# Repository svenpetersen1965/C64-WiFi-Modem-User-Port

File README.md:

# C64-WiFi-Modem-User-Port
A NodeMCU (ESP8266) based WiFi modem for the C64's user port
This is a Wifi-Modem for the Commodore C64 Uperport, which is based on the ESP8266 (NodeMCU v3). It contains level shifters to 
translate between the NodeMCU 3.3V level and the User Port 5V level. This prevents stressing the User Port due to a level mismatch.

Further on, status LEDs and (in Rev. 1) a Reset switch is contained.

About the NodeMCU v3: There is a version, which is wider. The version that work is WeMOS NodeMCU v3, which is about 25.4mm wide. You can compare it to this picture, please. The right one has the labeling of the pins parallel to the edge of the PCB. 

The wiring follows the instruction on https://1200baud.wordpress.com/2017/03/04/build-your-own-9600-baud-c64-wifi-modem-for-20/ 

The firmware, required for the NodeMCU, can be obtained from the same website. Please follow the setup procedure described there.

Now, the STL files for a 3D printed case are available for this project.

There are three types of reset switch plungers for some common tact switch heights (4.3mm, 5mm and 7mm).

Rev. 1 works well, but only accepts the (smaller) WeMos NodeMCU v3 (approximately 48mx25mm). There is a bigger version available from the common sales platforms, which are bigger: 31mm x 57mm and don't fit the footprint of Rev. 1. This led to Rev. 2, which is now tested and working completely. 

Both sizes of the NodeMCU

WiFi Modem Rev. 2 in case

A nice blog about this project can be found here: <a href="https://medium.com/@gozdnijezek/c64-wifi-modem-user-port-by-sven-petersen-commodore-wifi-modem-21ab0eed411d">GozdniJezek: C64-WiFi-Modem-User-Port by Sven Petersen (Commodore WiFi modem)</a>

# Recommended Screws
For the case, I have used 2.9mm x 9.5mm (self taping) screws for sheet metal (C 2,9x9,5H, DIN 7981). 

# Calculation of the Component prices
The prices of the components was summed up. The total costs without the 3D printed case and any shipping fees is 16.19€ (May 2020). This might differ, depending on the source of the parts the Node MCU v3 can be obtained from non-domestic sources for less.

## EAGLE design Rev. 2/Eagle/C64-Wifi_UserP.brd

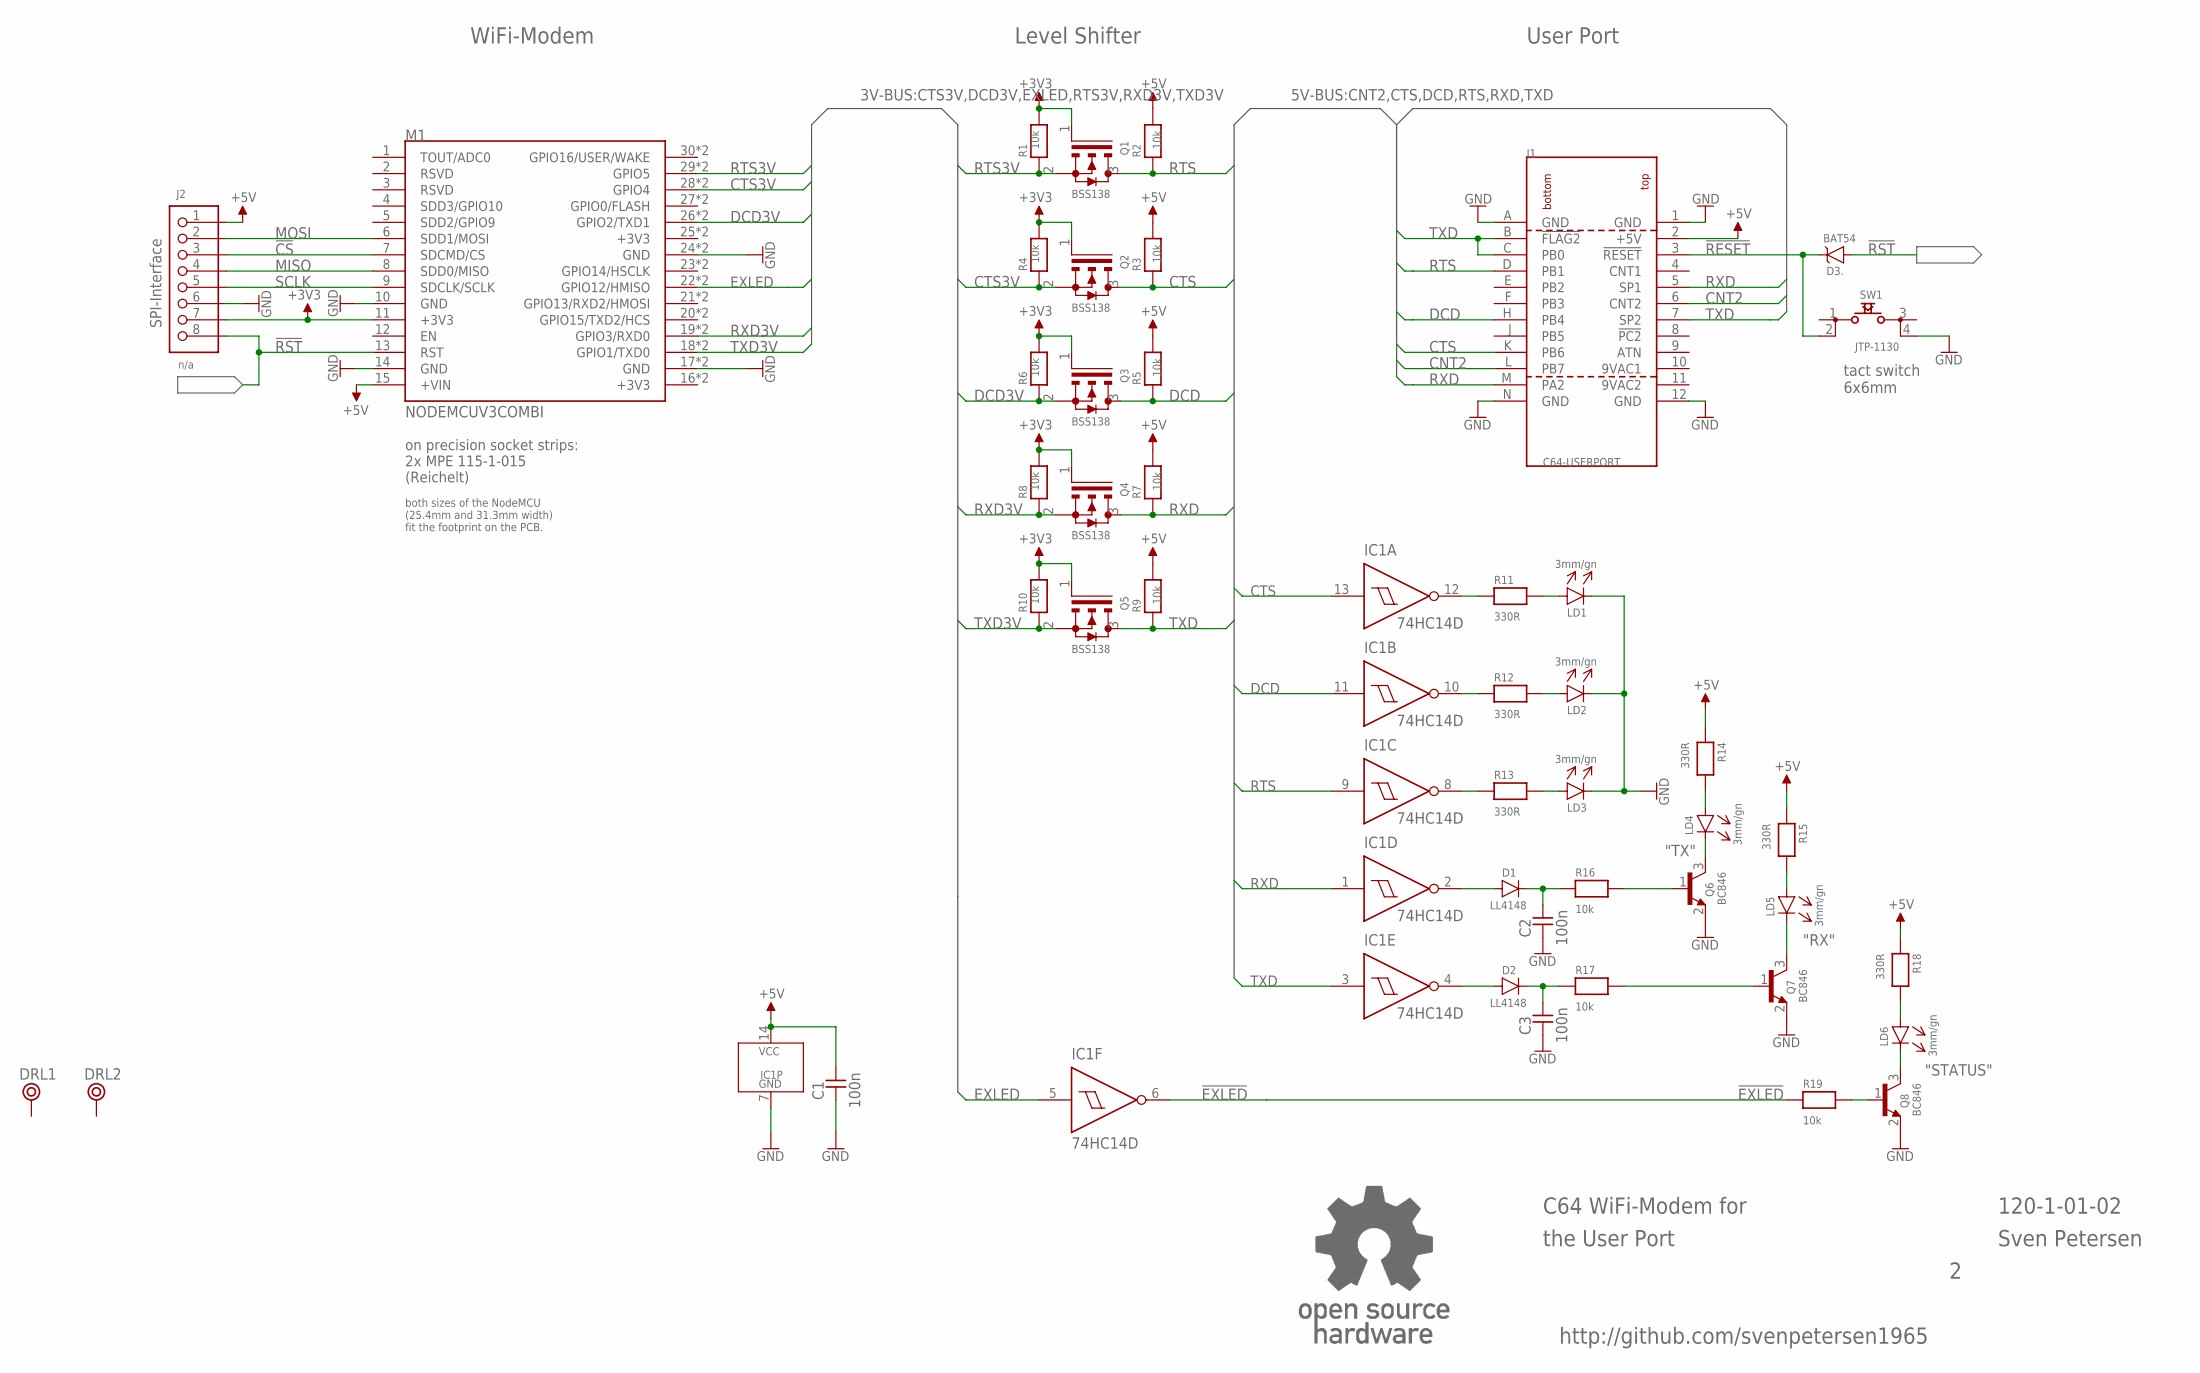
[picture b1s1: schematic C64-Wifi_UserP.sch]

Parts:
C1, C2, C3: 100n; 0805
D1, D2: LL4148; SOD80C
D3: BAT54; SOT23
DRL1, DRL2: BOHR3,3
IC1: 74HC14D; SO-14
J1: C64-USERPORT; USERPORT
J2: n/a; 1X08
LD1, LD2, LD3, LD4, LD5, LD6: 3mm/gn; 3MM
M1: NODEMCUV3COMBI; NODEMCUV3_X
Q1, Q2, Q3, Q4, Q5: BSS138; SOT23
Q6, Q7, Q8: BC846; SOT23
R1, R2, R3, R4, R5, R6, R7, R8, R9, R10, R16, R17, R19: 10k; 0805
R11, R12, R13, R14, R15, R18: 330R; 0805
SW1: JTP-1130
U$45: OPEN_SOURCE_HW; OPENHW

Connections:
9VAC1: J1.10 (9VAC1)
9VAC2: J1.11 (9VAC2)
!CS: J2.3, M1.7 (SDCMD/CS)
!EXLED: IC1.6 (O), R19.1
!RESET: D3.3 (K), J1.3 (!RESET), SW1.2
!RST: D3.1 (A), J2.8, M1.13 (RST)
+3V3: J2.7, M1.11 (+3V3), Q1.1 (G), Q2.1 (G), Q3.1 (G), Q4.1 (G), Q5.1 (G), R1.2, R4.2, R6.2, R8.2, R10.2
+5V: C1.2, IC1.14 (VCC), J1.2 (+5V), J2.1, M1.15 (+VIN), R2.2, R3.2, R5.2, R7.2, R9.2, R14.1, R15.1, R18.1
CNT2: J1.6 (CNT2), J1.L (PB7)
CTS: IC1.13 (I), J1.K (PB6), Q2.3 (D), R3.1
CTS3V: M1.28 (GPIO4), M1.28W (GPIO4), Q2.2 (S), R4.1
DCD: IC1.11 (I), J1.H (PB4), Q3.3 (D), R5.1
DCD3V: M1.26 (GPIO2/TXD1), M1.26W (GPIO2/TXD1), Q3.2 (S), R6.1
EXLED: IC1.5 (I), M1.22 (GPIO12/HMISO), M1.22W (GPIO12/HMISO)
GND: C1.1, C2.1, C3.1, IC1.7 (GND), J1.1 (GND), J1.12 (GND), J1.A (GND), J1.N (GND), J2.6, LD1.C (K), LD2.C (K), LD3.C (K), M1.10 (GND), M1.14 (GND), M1.17 (GND), M1.17W (GND), M1.24 (GND), M1.24W (GND), Q6.2 (E), Q7.2 (E), Q8.2 (E), SW1.4
MISO: J2.4, M1.8 (SDD0/MISO)
MOSI: J2.2, M1.6 (SDD1/MOSI)
unnamed: IC1.12 (O), R11.1
unnamed: IC1.10 (O), R12.1
unnamed: IC1.8 (O), R13.1
unnamed: D1.A, IC1.2 (O)
unnamed: D2.A, IC1.4 (O)
unnamed: LD5.A, R15.2
unnamed: LD4.A, R14.2
unnamed: LD3.A, R13.2
unnamed: LD2.A, R12.2
unnamed: LD1.A, R11.2
unnamed: C2.2, D1.K, R16.1
unnamed: C3.2, D2.K, R17.1
unnamed: Q6.1 (B), R16.2
unnamed: Q7.1 (B), R17.2
unnamed: LD4.C (K), Q6.3 (C)
unnamed: LD5.C (K), Q7.3 (C)
unnamed: LD6.A, R18.2
unnamed: LD6.C (K), Q8.3 (C)
unnamed: Q8.1 (B), R19.2
RTS: IC1.9 (I), J1.D (PB1), Q1.3 (D), R2.1
RTS3V: M1.29 (GPIO5), M1.29W (GPIO5), Q1.2 (S), R1.1
RXD: IC1.1 (I), J1.5 (SP1), J1.M (PA2), Q4.3 (D), R7.1
RXD3V: M1.19 (GPIO3/RXD0), M1.19W (GPIO3/RXD0), Q4.2 (S), R8.1
SCLK: J2.5, M1.9 (SDCLK/SCLK)
TXD: IC1.3 (I), J1.7 (SP2), J1.B (!FLAG2), J1.C (PB0), Q5.3 (D), R9.1
TXD3V: M1.18 (GPIO1/TXD0), M1.18W (GPIO1/TXD0), Q5.2 (S), R10.1

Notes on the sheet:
WiFi-Modem
Level Shifter
User Port
C64 WiFi-Modem for
the User Port
120-1-01-02
Sven Petersen
on precision socket strips: 2x MPE 115-1-015 (Reichelt)
"TX"
"RX"
"STATUS"
SPI-Interface
both sizes of the NodeMCU (25.4mm and 31.3mm width) fit the footprint on the PCB.
http://github.com/svenpetersen1965
tact switch 6x6mm

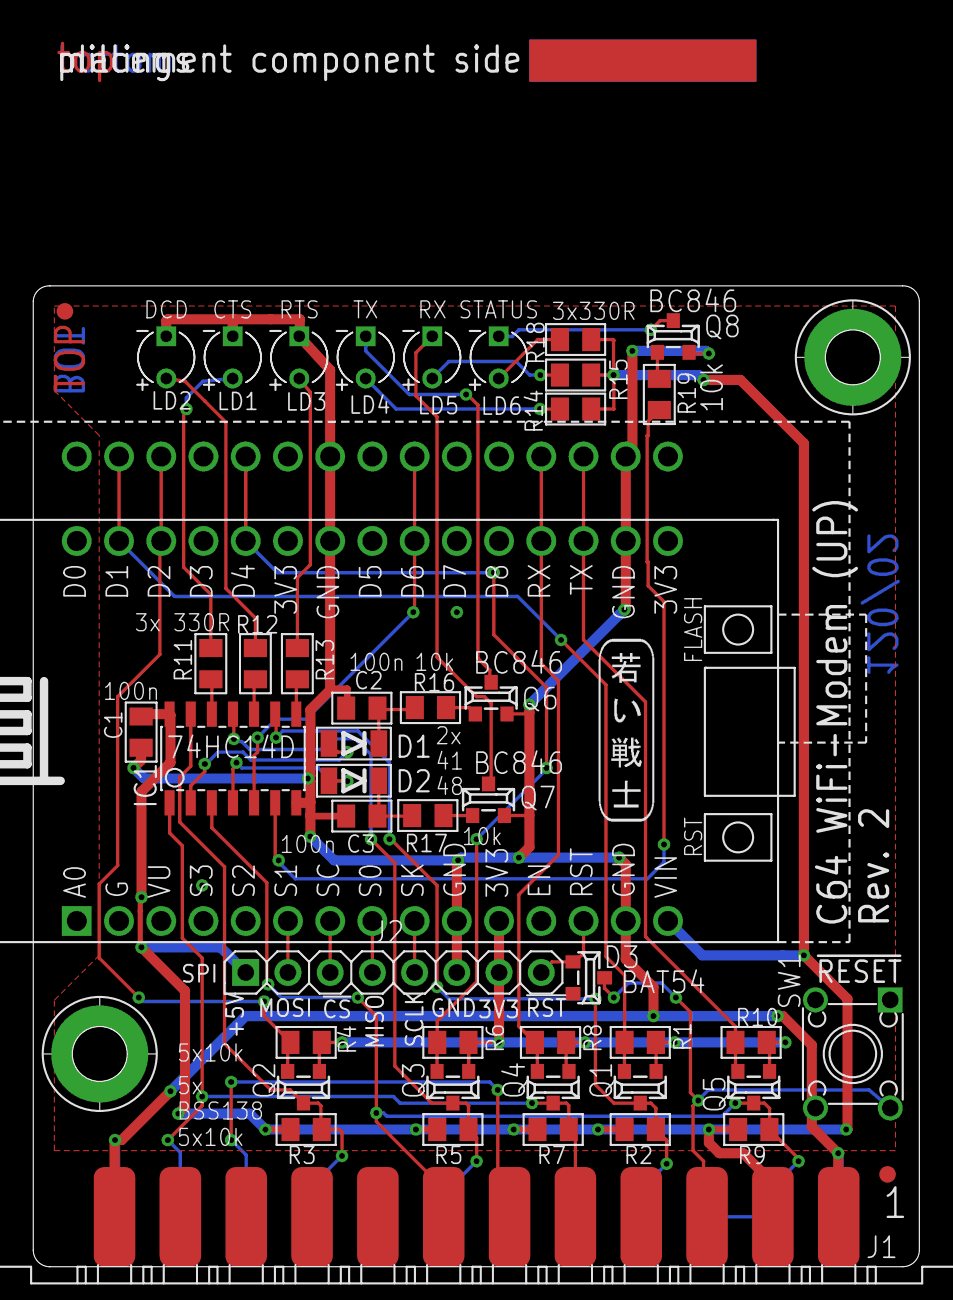
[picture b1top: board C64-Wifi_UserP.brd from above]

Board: 2 copper layers, 53.2 x 74.1 mm, 52 parts (1 on the bottom side), 41 nets.

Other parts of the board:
U$36: PCB-TITLE/
U$37: 2LAYER
U$38, U$39: SMD_REF_R1MM
U$44: SVEN_TAG

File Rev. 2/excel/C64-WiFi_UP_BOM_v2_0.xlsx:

C64 WiFi-Modem for User Port Rev. 2
Bill of Material Rev. 2.0
Pos. | Qty | Value | Footprint | Ref.-No. | Comment
1 | 1 | 120-2-01-01 | 2 Layer | PCB Rev. 1 | 2 layer, Cu 35µ, HASL, 54.0 x 53.3, 1.6mm FR4
2 | 6 | 3mm/gn | 3mm LED | LD1, LD2, LD3, LD4, LD5, LD6 | Standard 3mm green LEDs
3 | 3 | 100n | 0805 | C1, C2, C3 | ceramic cap, 0805, 25V or better
4 | 13 | 10k | 0805 | R1, R2, R3, R4, R5, R6, R7, R8, R9, R10, R16, R17, R19 | chip resistor, 0805, 5% or better
5 | 6 | 330R | 0805 | R11, R12, R13, R14, R15, R18 | chip resistor, 0805, 5% or better
6 | 1 | 74HC14D | SO-14 | IC1 | ST micro, NXP, TI etc. e.g. Reichelt SMD HC 14
7 | 3 | BC846B | SOT23 | Q6, Q7, Q8 | SMD NPN transistor, e.g. Reichelt BC 846B NXP
8 | 5 | BSS138 | SOT23 | Q1, Q2, Q3, Q4, Q5 | SMD MOSFET, e.g. Reichelt BSS 138 SMD
9 | 1 | 2x12, 3.96mm pitch | USERPORT | J1 | edge connector for C64 user port, ebay or online shops
10 | 2 | LL4148 | SOD80C | D1, D2 | diode SMD, e.g. Reichelt LL4148
11 | 1 | NodeMCU V3 | NODEMCUV3 | M1 | e.g. WeMOS NodeMCU v3. ebay or online shops or Reichelt DEBO JT ESP8266, either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
12 | 2 | socket strip 15p. 2.54mm pitch |  | (M1) | e.g. MPE Garry 115-1-015, Reichelt MPE 115-1-015
13 | 1 | 8p, 2.54mm pin header |  | J2 | not populated
14 | 1 | BAT54 | SOT23 | D3 | schottky diode
15 | 1 | JTP-1130 | 6mm tact switch | SW1 | Namea Electronics. Or standard 6x6mm tact switch
 |  | Rev. 0 -> Rev. 1
Pos. | 1 | Board Revision
Pos. | 2 | changed to 3mm led
Pos. | 13 | new
Pos. | 14 | new
Pos. | 15 | new
 |  | Rev. 1 -> 2
Pos. | 1 | Board Revision

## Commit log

2019-10-15 Case added for the revision 0 or the PCB
2019-11-07 Testing v1.1 added to the document
2020-03-20 Case for PCB Rev. 2 released, rearranged directories
2020-03-20 Rev. 2 released
2020-06-09 Calculation of the component prices
    A calculation of the component prices was added (June 8th, 2020)
2020-08-10 Silk Screen Update
2020-08-17 PicknPlace in mm and inch
2021-06-03 Label as PNG file.
2022-02-26 Gerbers removed
2026-05-02 Gerbers without document frame
